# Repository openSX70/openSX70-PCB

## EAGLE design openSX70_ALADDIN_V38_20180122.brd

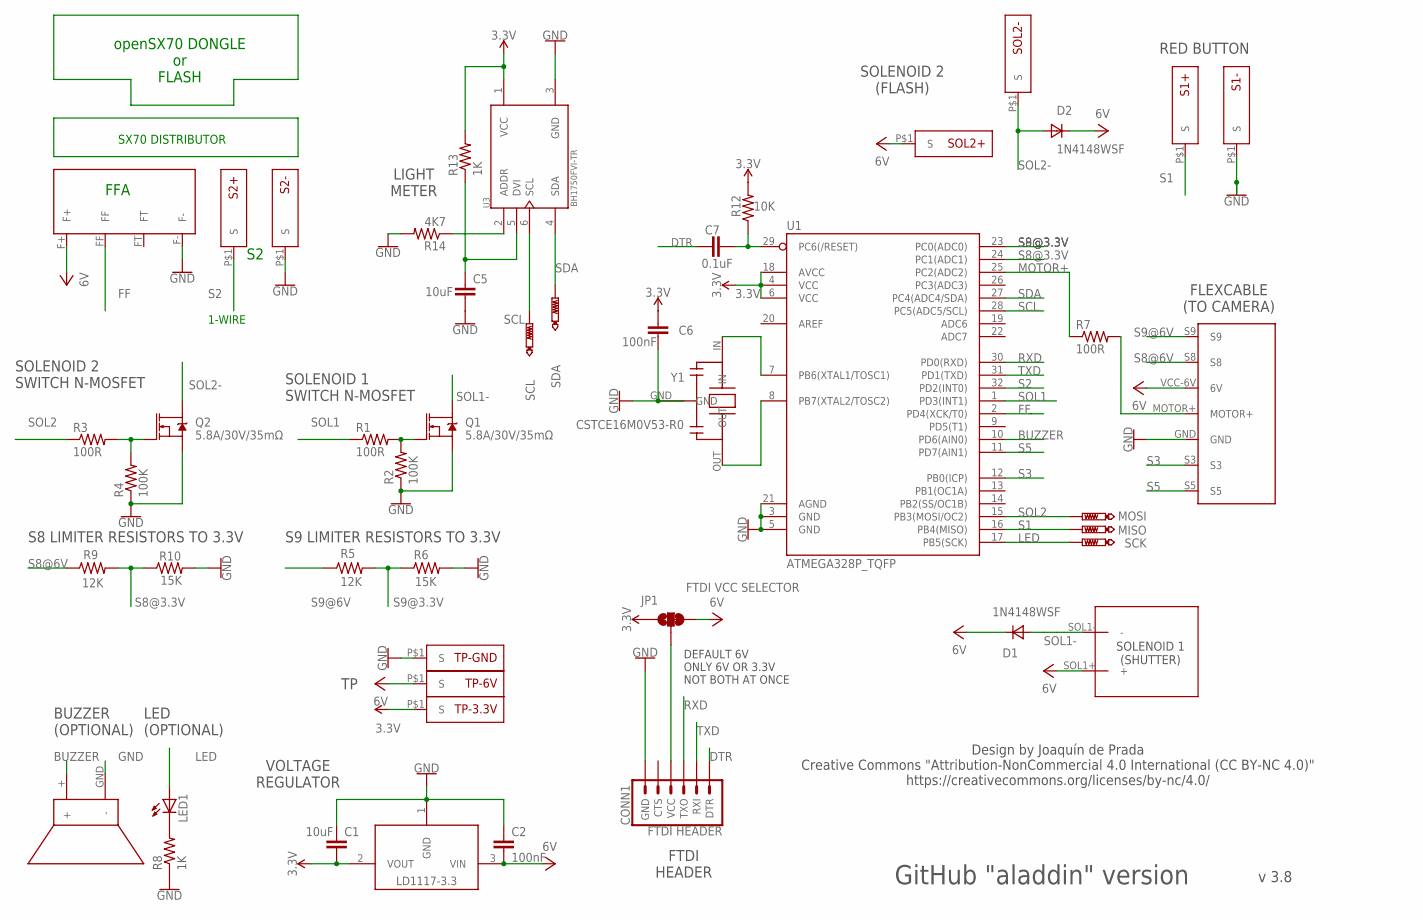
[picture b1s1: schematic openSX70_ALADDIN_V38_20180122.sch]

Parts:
BUZZ1: CSET8-5G; CSET8-5G_PACKAGE
C1, C5: 10uF; 0603
C2: 100nF; C0603K
C6: 100nF; C0603
C7: 0.1uF; 0603
CONN1: FTDI HEADER; 1X06
D1, D2: 1N4148WSF; SOD323
JP1: FTDI VCC SELECTOR; SMT-JUMPER_3_1-NC_TRACE_SILK
LD11173.3V: LD1117 3.3V; SOT223
LED1: LEDCHIPLED_0805; CHIPLED_0805
MISO: PTR1TP08R; TP08R
MOSI: PTR1TP08R; TP08R
Q1, Q2: 5.8A/30V/35mΩ; SOT23-3
R1, R3, R7: 100R; R0603
R2, R4: 100K; R0603
R5, R9: 12K; R0603
R6, R10: 15K; R0603
R8, R13: 1K; R0603
R12: 10K; R0603
R14: 4K7; R0603
S1+, S1-, S2+, S2-: SX70-S-PAD-NEW; SX70-S-PAD2
SCK: PTR1TP08R; TP08R
SCL: PTR1TP08R; TP08R
SDA: PTR1TP08R; TP08R
SOL1: SX70-SOLENOID1-2PADS; SX70-SOLENOID1-2
SOL2+, SOL2-: SX70-S-PAD-NEW; SX70-S-PAD2
TP-3.3V, TP-6V: SX70-S-PAD-NEW; SX70-S-PAD2
TP-GND: SX70-S-PAD-NEW; SX70-S-PAD2
U1: ATMEGA328P_TQFP; TQFP32-08
U3: BH1750FVI-TR; SOTFL50P300X75-6N
U$1: SX70-7-PAD
U$2: FFA; FFA-PAD-PACKAGE
Y1: CSTCE16M0V53-R0; CFP95P160X100-3N

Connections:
3.3V: C1.2, C6.1, JP1.1, LD11173.3V.2 (VOUT), R12.2, R13.2, TP-3.3V.P$1, U1.4 (VCC), U1.6 (VCC), U1.18 (AVCC), U3.1 (VCC)
6V: C2.2, D1.1 (C), D2.1 (C), JP1.3, LD11173.3V.3 (VIN), SOL1.SOL1+ (+), SOL2+.P$1, TP-6V.P$1, U$1.VCC-6V (6V), U$2.F+
BUZZER: BUZZ1.+, U1.10 (PD6(AIN0))
DTR: C7.1, CONN1.1 (DTR)
FF: U1.2 (PD4(XCK/T0)), U$2.FF
GND: BUZZ1.GND (-), C1.1, C2.1, C5.2, C6.2, CONN1.6 (GND), LD11173.3V.1 (GND), Q1.2 (S), Q2.2 (S), R2.1, R4.1, R6.2, R8.1, R10.2, R14.2, S1-.P$1, S2-.P$1, TP-GND.P$1, U1.3 (GND), U1.5 (GND), U1.21 (AGND), U3.3 (GND), U$1.GND, U$2.F-, Y1.GND
LED: LED1.A, SCK.TP, U1.17 (PB5(SCK))
MOTOR+: R7.1, U1.25 (PC2(ADC2))
MOTOR-HEADER: R7.2, U$1.MOTOR+
unnamed: Q1.1 (G), R1.2, R2.2
unnamed: C5.1, R13.1, U3.5 (DVI)
unnamed: Q2.1 (G), R3.2, R4.2
unnamed: U1.7 (PB6(XTAL1/TOSC1)), Y1.IN
unnamed: LED1.C, R8.2
unnamed: U1.8 (PB7(XTAL2/TOSC2)), Y1.OUT
unnamed: C7.2, R12.1, U1.29 (PC6(/RESET))
unnamed: R14.1, U3.2 (ADDR)
unnamed: CONN1.4 (VCC), JP1.2
RXD: CONN1.3 (TXO), U1.30 (PD0(RXD))
S1: MISO.TP, S1+.P$1, U1.16 (PB4(MISO))
S2: S2+.P$1, U1.32 (PD2(INT0))
S3: U1.12 (PB0(ICP)), U$1.S3
S5: U1.11 (PD7(AIN1)), U$1.S5
S8@3.3V: R9.2, R10.1, U1.24 (PC1(ADC1))
S8@6V: R9.1, U$1.S8
S9@3.3V: R5.2, R6.1, U1.23 (PC0(ADC0))
S9@6V: R5.1, U$1.S9
SCL: SCL.TP, U1.28 (PC5(ADC5/SCL)), U3.6 (SCL)
SDA: SDA.TP, U1.27 (PC4(ADC4/SDA)), U3.4 (SDA)
SOL1: R1.1, U1.1 (PD3(INT1))
SOL1-: D1.2 (A), Q1.3 (D), SOL1.SOL1- (-)
SOL2: MOSI.TP, R3.1, U1.15 (PB3(MOSI/OC2))
SOL2-: D2.2 (A), Q2.3 (D), SOL2-.P$1
TXD: CONN1.2 (RXI), U1.31 (PD1(TXD))

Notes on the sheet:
1-WIRE
FFA
LIGHT METER
FLEXCABLE (TO CAMERA)
RED BUTTON
SOLENOID 1 (SHUTTER)
SOLENOID 2 (FLASH)
FTDI HEADER
VOLTAGE REGULATOR
BUZZER (OPTIONAL)
LED (OPTIONAL)
S8 LIMITER RESISTORS TO 3.3V
S9 LIMITER RESISTORS TO 3.3V
SOLENOID 2 SWITCH N-MOSFET
SOLENOID 1 SWITCH N-MOSFET
SX70 DISTRIBUTOR
openSX70 DONGLE or FLASH
v 3.8
Design by Joaquín de Prada Creative Commons "Attribution-NonCommercial 4.0 International (CC BY-NC 4.0)" https://creativecommons.org/licenses/by-nc/4.0/
GitHub "aladdin" version
DEFAULT 6V ONLY 6V OR 3.3V NOT BOTH AT ONCE

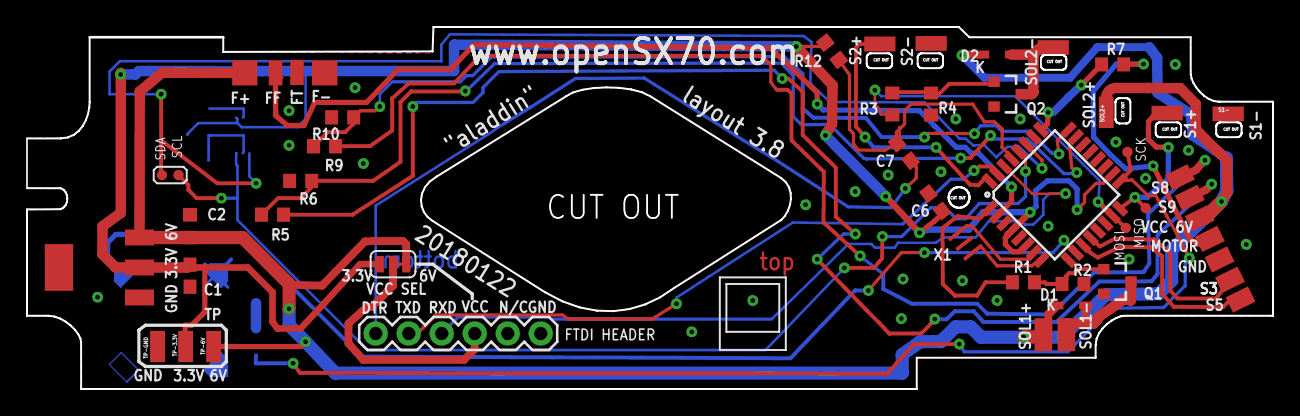
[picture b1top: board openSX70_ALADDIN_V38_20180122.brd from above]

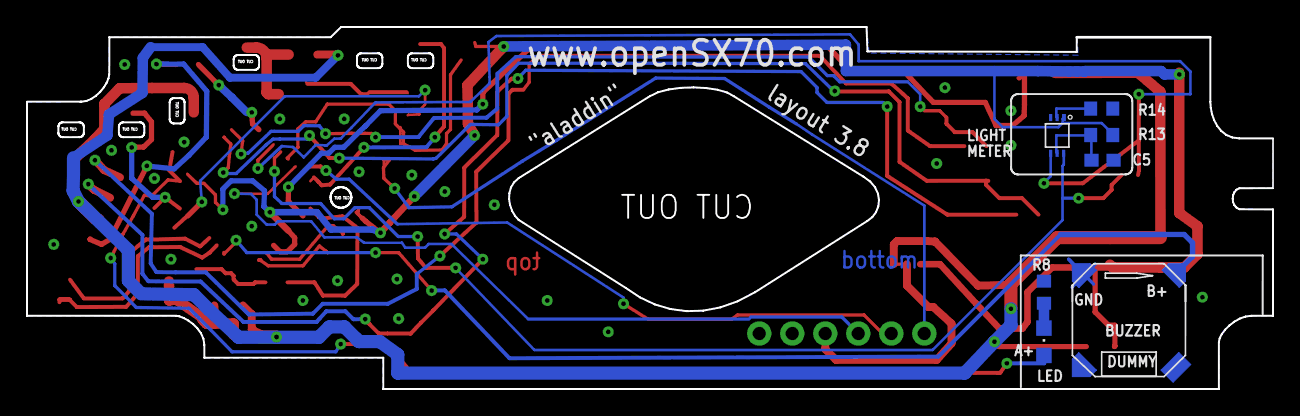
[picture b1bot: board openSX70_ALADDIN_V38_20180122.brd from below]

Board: 2 copper layers, 95.9 x 27.9 mm, 47 parts (7 on the bottom side), 34 nets.

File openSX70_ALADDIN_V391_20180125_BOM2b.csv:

Qty,Value,Device,Package,Parts,Description,,
1,,LEDCHIPLED_0805,CHIPLED_0805,LED1,LED,,
1,0.1uF,0.1UF-0603-25V-(+80/-20%),0603,C7,0.1µF ceramic capacitors,,
2,100K,R-US_R0603,R0603,R2, R4,RESISTOR, American symbol,,
3,100R,R-US_R0603,R0603,R1, R3, R7,RESISTOR, American symbol,,
1,100nF,C-EUC0603,C0603,C6,CAPACITOR, European symbol,,
1,100nF,C-EUC0603K,C0603K,C2,CAPACITOR, European symbol,,
3,10K,R-US_R0603,R0603,R6, R10, R12,RESISTOR, American symbol,,
2,10uF,10UF-0603-6.3V-20%,0603,C1, C5,10.0µF ceramic capacitors,,
2,15K,R-US_R0603,R0603,R5, R9,RESISTOR, American symbol,,
2,1K,R-US_R0603,R0603,R8, R13,RESISTOR, American symbol,,
2,1N4148WSF,DSOD323,SOD323,D1, D2,DIODE,,
1,4K7,R-US_R0603,R0603,R14,RESISTOR, American symbol,,
2,5.8A/30V/35mO,MOSFET-NCH-AO3404A,SOT23-3,Q1, Q2,N-channel MOSFETs,,
1,ATMEGA328P_TQFP,ATMEGA328P_TQFP,TQFP32-08,U1,Popular 328P in QFP,,
1,BH1750FVI-TR,BH1750FVI-TR,SOTFL50P300X75-6N,U3,Light to Digital Ambient Light Sensor Digital O/P 1lux to 65535lux 6-Pin WSOF Embossed T/R,,
1,CSET8-5G,CSET8-5G,CSET8-5G_PACKAGE,BUZZ1,,,
1,CSTCE16M0V53-R0,CSTCE16M0V53-R0,CFP95P160X100-3N,Y1,Ceramic Resonator 16MHz ±0.5% (Tol) ±0.3% (Stability) 15pF 40Ohm 3-Pin CSMD T/R,,
1,FFA,SX70-FFA-PAD,FFA-PAD-PACKAGE,U$2,,,
1,FTDI VCC SELECTOR,JUMPER-SMT_3_1-NC_TRACE_SILK,SMT-JUMPER_3_1-NC_TRACE_SILK,JP1,Normally closed trace jumper (1 of 2 connections),,
1,GND,XF2L-0625-1,XF2L-0625-1,J1,OMRON FPC Connector,,
1,LD1117 2.5V,LD1117-3.3,SOT223,LD11172.5V,,,
5,PTR1TP08R,PTR1TP08R,TP08R,MISO, MOSI, SCK, SCL, SDA,TEST PIN,,

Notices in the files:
parts and their libraries:
SparkFun-Capacitors: Licensing: Creative Commons ShareAlike 4.0 International - https://creativecommons.org/licenses/by-sa/4.0
